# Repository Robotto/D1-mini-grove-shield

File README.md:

# The boards look like this:

# Kicanvas links:

## [ESP8266 version](https://kicanvas.org/?github=https%3A%2F%2Fgithub.com%2FRobotto%2FD1-mini-grove-shield/tree/main/8266)

## [ESP32 version](https://kicanvas.org/?github=https%3A%2F%2Fgithub.com%2FRobotto%2FD1-mini-grove-shield/tree/main/32)

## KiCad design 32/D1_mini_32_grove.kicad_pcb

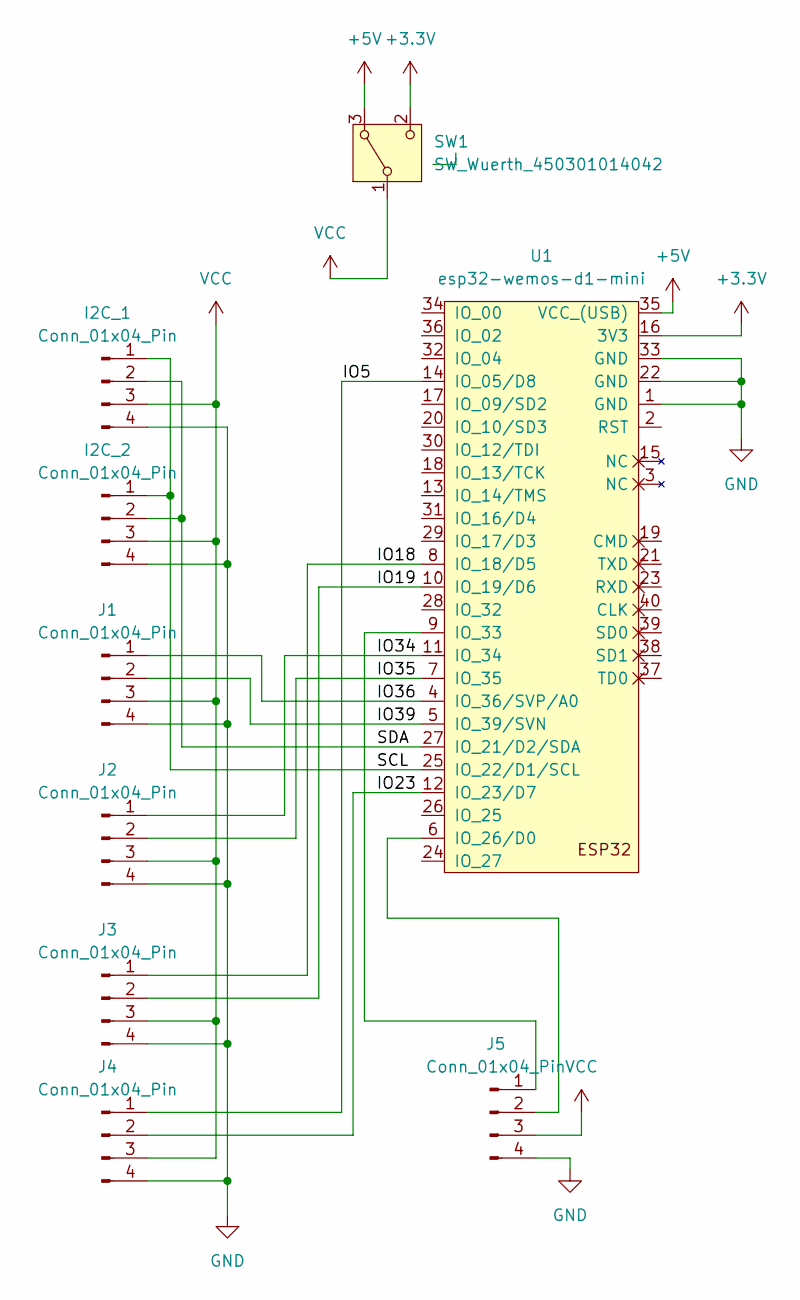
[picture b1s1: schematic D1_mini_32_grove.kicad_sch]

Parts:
I2C_1, I2C_2: Conn_01x04_Pin; NS-Tech_Grove_1x04_P2mm_Vertical
J1, J2, J3, J4, J5: Conn_01x04_Pin; NS-Tech_Grove_1x04_P2mm_Vertical
SW1: SW_Wuerth_450301014042; SW_Slide-03_Wuerth-WS-SLTV_10x2.5x6.4_P2.54mm
U1: esp32-wemos-d1-mini

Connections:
+3.3V: SW1.2 (C), U1.16 (3V3)
+5V: SW1.3 (A), U1.35 (VCC_(USB))
/IO5: J4.1, U1.14 (IO_05/D8)
/IO18: J3.1, U1.8 (IO_18/D5)
/IO19: J3.2, U1.10 (IO_19/D6)
/IO23: J4.2, U1.12 (IO_23/D7)
/IO34: J2.1, U1.11 (IO_34)
/IO35: J2.2, U1.7 (IO_35)
/IO36: J1.1, U1.4 (IO_36/SVP/A0)
/IO39: J1.2, U1.5 (IO_39/SVN)
/SCL: I2C_1.1, I2C_2.1, U1.25 (IO_22/D1/SCL)
/SDA: I2C_1.2, I2C_2.2, U1.27 (IO_21/D2/SDA)
GND: I2C_1.4, I2C_2.4, J1.4, J2.4, J3.4, J4.4, J5.4, U1.1 (GND), U1.22 (GND), U1.33 (GND)
unnamed: J5.1, U1.9 (IO_33)
unnamed: J5.2, U1.6 (IO_26/D0)
VCC: I2C_1.3, I2C_2.3, J1.3, J2.3, J3.3, J4.3, J5.3, SW1.1 (B)

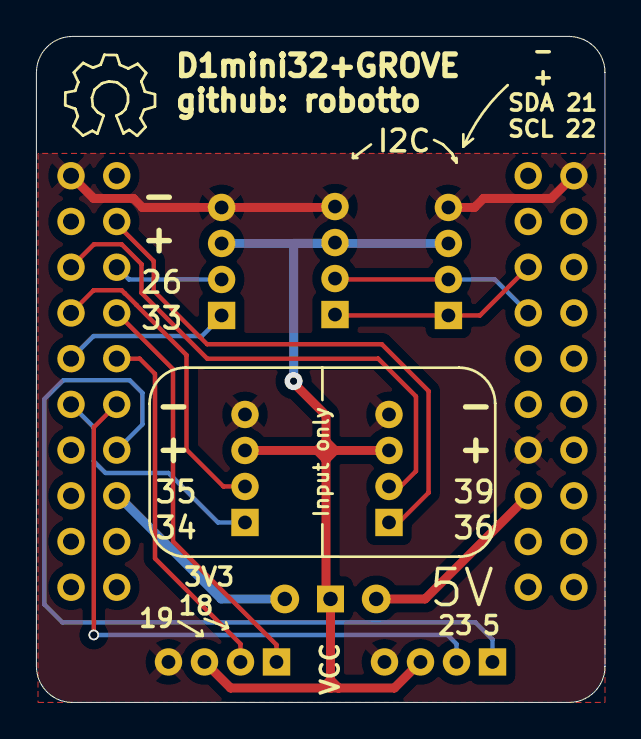
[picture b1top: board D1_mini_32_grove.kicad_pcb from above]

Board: 2 copper layers, 31.6 x 37.0 mm, 9 parts (0 on the bottom side), 16 nets.

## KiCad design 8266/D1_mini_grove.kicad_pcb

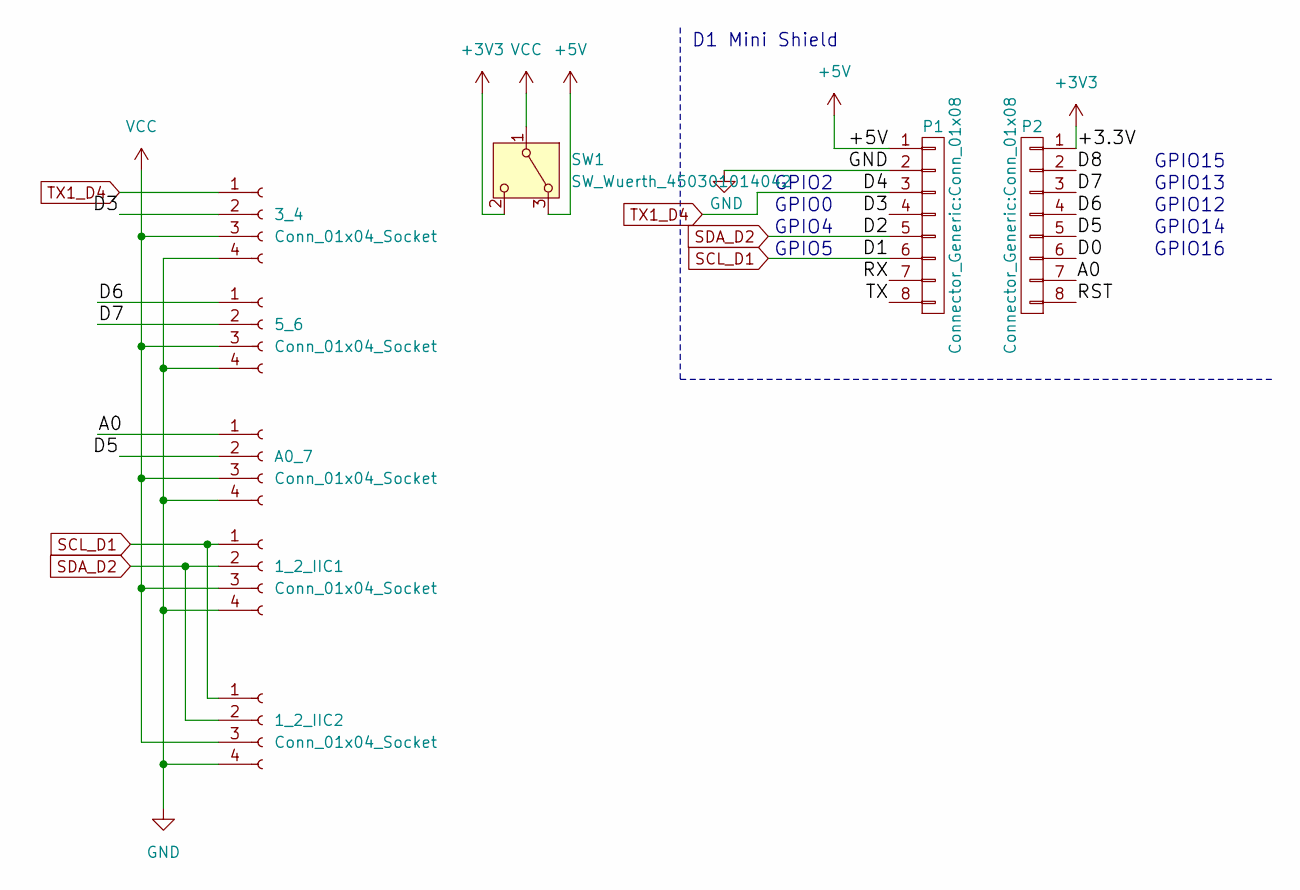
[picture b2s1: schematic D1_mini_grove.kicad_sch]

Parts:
1_2_IIC1, 1_2_IIC2, 3_4, 5_6: Conn_01x04_Socket; NS-Tech_Grove_1x04_P2mm_Vertical
A0_7: Conn_01x04_Socket; NS-Tech_Grove_1x04_P2mm_Vertical
P1, P2: Connector_Generic:Conn_01x08; D1_mini_Pin_Header
SW1: SW_Wuerth_450301014042; SW_Slide-03_Wuerth-WS-SLTV_10x2.5x6.4_P2.54mm

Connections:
+3V3: P2.1, SW1.2 (C)
+5V: P1.1, SW1.3 (A)
/A0: A0_7.1, P2.7
/D0: P2.6
/D3: 3_4.2, P1.4
/D5: A0_7.2, P2.5
/D6: 5_6.1, P2.4
/D7: 5_6.2, P2.3
/D8: P2.2
/RST: P2.8
/RX: P1.7
/TX: P1.8
GND: 1_2_IIC1.4, 1_2_IIC2.4, 3_4.4, 5_6.4, A0_7.4, P1.2
SCL_D1: 1_2_IIC1.1, 1_2_IIC2.1, P1.6
SDA_D2: 1_2_IIC1.2, 1_2_IIC2.2, P1.5
TX1_D4: 3_4.1, P1.3
VCC: 1_2_IIC1.3, 1_2_IIC2.3, 3_4.3, 5_6.3, A0_7.3, SW1.1 (B)

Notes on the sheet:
GPIO12
GPIO2
GPIO16
GPIO13
GPIO4
GPIO15
D1 Mini Shield
GPIO5
GPIO0
GPIO14

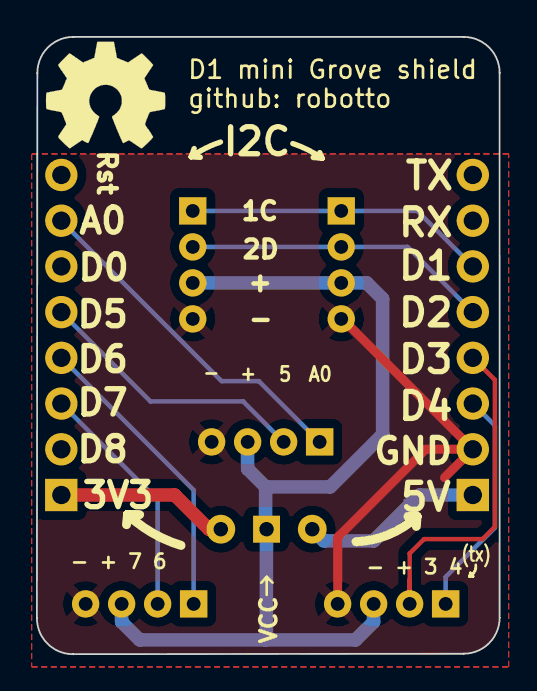
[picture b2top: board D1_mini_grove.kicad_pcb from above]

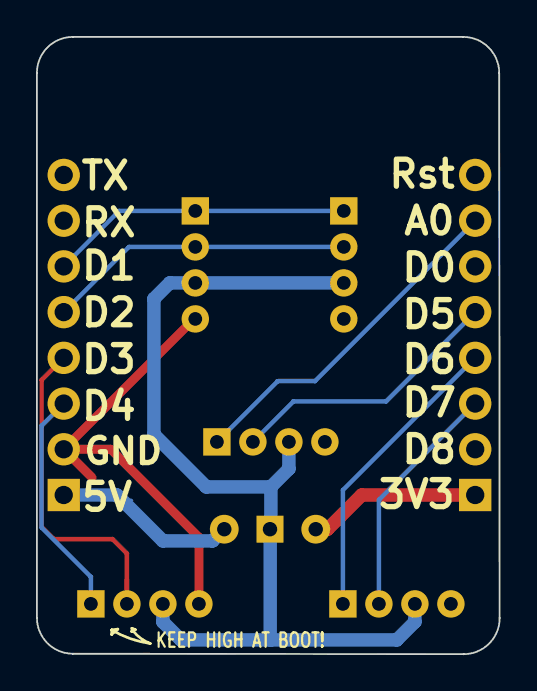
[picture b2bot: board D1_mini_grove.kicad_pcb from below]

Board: 2 copper layers, 25.7 x 34.3 mm, 8 parts (2 on the bottom side), 12 nets.

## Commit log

2024-10-30 init
2024-10-30 Added 3D view of board
2024-10-30 Create README.md
    Added README -> Added 3D view to README
2024-10-30 forgot to commit footprint library table
2024-10-30 Added kicanvas link
2024-10-31 Topsilk rearranged, shoud fix #1
2024-10-31 updated 3D view
2024-11-07 flipped some stuff around
2024-11-07 Fiddled with grove connector footprint silk
2024-11-07 Finetuned some layout
2024-11-17 moved ESP8266 project to subfolder, getting ready for ESP32 version
2024-11-17 i like to move it move it
2024-11-17 started doing the ESP32 version, don't trust anything yet
2024-11-18 First draft of 32 board ready for testrun
2024-11-18 last commit din't take because i'm messing around with upstream stuff
2024-11-18 moved small things, sent gerbers to pcbway
2024-11-28 bigger holes for pin header rows
2025-03-23 Added a switch for VCC selector instead of solder bridge.. its tight but itll work
2025-03-24 Messing with silkscreen, mostly
2025-03-24 The 32board had room for one more grove connector... finetuned some 3D stuff too
2025-03-24 Production run for 8266 board as well.
2025-03-24 Fresh 3D views
2025-03-24 Cleanup
2025-03-24 safety
2025-03-25 Set 3D model dir to relaive path, flipped entire 8266 board around so it sits right in my mind
2025-03-25 3D previews in README
2025-03-25 trying stuff with step file previews
2025-03-25 3D stuff
2025-03-25 Markdown
2025-09-29 Second production run
2025-09-29 Safety commit
2026-03-05 Slighly modified layout for 3rd production run
2026-03-26 Added silkscreen info about input only pins
